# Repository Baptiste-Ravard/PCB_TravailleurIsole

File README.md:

# PCB_TravailleurIsole

# Présentation du projet :

Le projet consiste à fabriquer un badge pour les travailleurs isolés.

Celui-ci a pour but de détecter si le travailleur qui le porte fait un malaise et enverrait un signal d'alarme ainsi que la position du travailleur à l'accueil pour qu'ils puissent prévenir les secours.

Pour ce faire, on aura besoin d'un capteur d'accélération, d'un GPS et d'un LoRaWan pour envoyer les alertes.

On établit une accélération seuil selon x,y,z. Si la valeur donnée par le capteur dépasse ce seuil, on considère que le travailleur a chuté : un premier signal est envoyé à l'utilisateur. Concrètement : une LED s'allume sur le badge. L'utilisateur a alors une durée ts de quelques secondes pour appuyer sur le bouton "fausse alerte" s'il a juste trébuché ou s'il n'est pas en danger. Ce bouton va alors réinitialiser le programme et aucune alerte ne sera envoyée à l'accueil.
Si au bout de ts l'utilisateur n'a pas appuyé sur le bouton de fausse alerte, on considère que le travailleur est en danger : le badge envoie donc grâce au LoRaWan la position donnée par le GPS ainsi qu'un message d'alarme à l'accueil. Le personnel présent pourra alors prévenir les secours pour lui venir en aide.

# Lien des différentes parties du projet :
Lien ressources LoRaWan :https://github.com/OliverBELLIARD/LoRaWAN.

Lien ressources batterie :https://github.com/inassra/batterie.

Lien ressources accéléromètre et GPS :https://github.com/ValerianPRIOU/Badge-pour-travailleur-isole

# Elements à ajouter au projet :

Ajouter un buzzer qui fait du bruit quand la première alerte est envoyée pour que le travailleur s'en rende compte et puisse appuyer sur le bouton si c'est une fausse alerte.

Ajouter un deuxième bouton afin que le travailleur puisse prévenir lui même s'il ne se sent pas bien.

Valeur seuil de l'accélération complètement à revoir, notre projet était surtout basé sur la conception du PCB et faire le code pour le LoRaWan, l'accéléromètre et le GPS donc on a mit une valeur en ordre de grandeur sans trop s'y attarder. Peut être que modifier le code pour prendre la vitesse (en dérivant) au lieu de l'accélération serait une bonne piste à explorer. Prendre en compte la position selon l'axe z et étudier des différences de potentiels est aussi une idée que l'on souhaitait développer. En effet lors d'un malaise la variation de vitesse n'est pas si grande (la chute ne dure qu'1m pour le capteur) et l'accélération seuil peut se confondre avec l'accélération d'un travailleur qui passe d'une vitesse nulle à une vitesse de marche(~7km/h) ou à une vitesse de course (~12 km/h)

Notre accélération finale est la norme des accélérations selon les axes x, y et z. Ne considérer que l'accélération selon z peut aussi être envisagé.

Pour le schéma et le board du PCB, ne pas oublier de rajouter un via permettant de relier les plans de masse du dessus et du dessous du PCB. Si ce n'est pas fait les régulateurs vont sauter à cause du microprocesseur qui ne recevra pas la bonne tension.

# Ce que nous a apporté le projet :

Pendant ce projet, nous avons appris à souder, déssouder (lors des erreurs), créer un PCB complexes et les erreurs pouvants etre faites.
Nous avons aussi appris à travailler avec des personnes qu'on ne connassait pas. En tant qu'intégrateur, nous devions donner des deadlines, prendre connaissance des avancements dans chacune des équipes, mettre en connexion ces équipes et les aider si necessaire.

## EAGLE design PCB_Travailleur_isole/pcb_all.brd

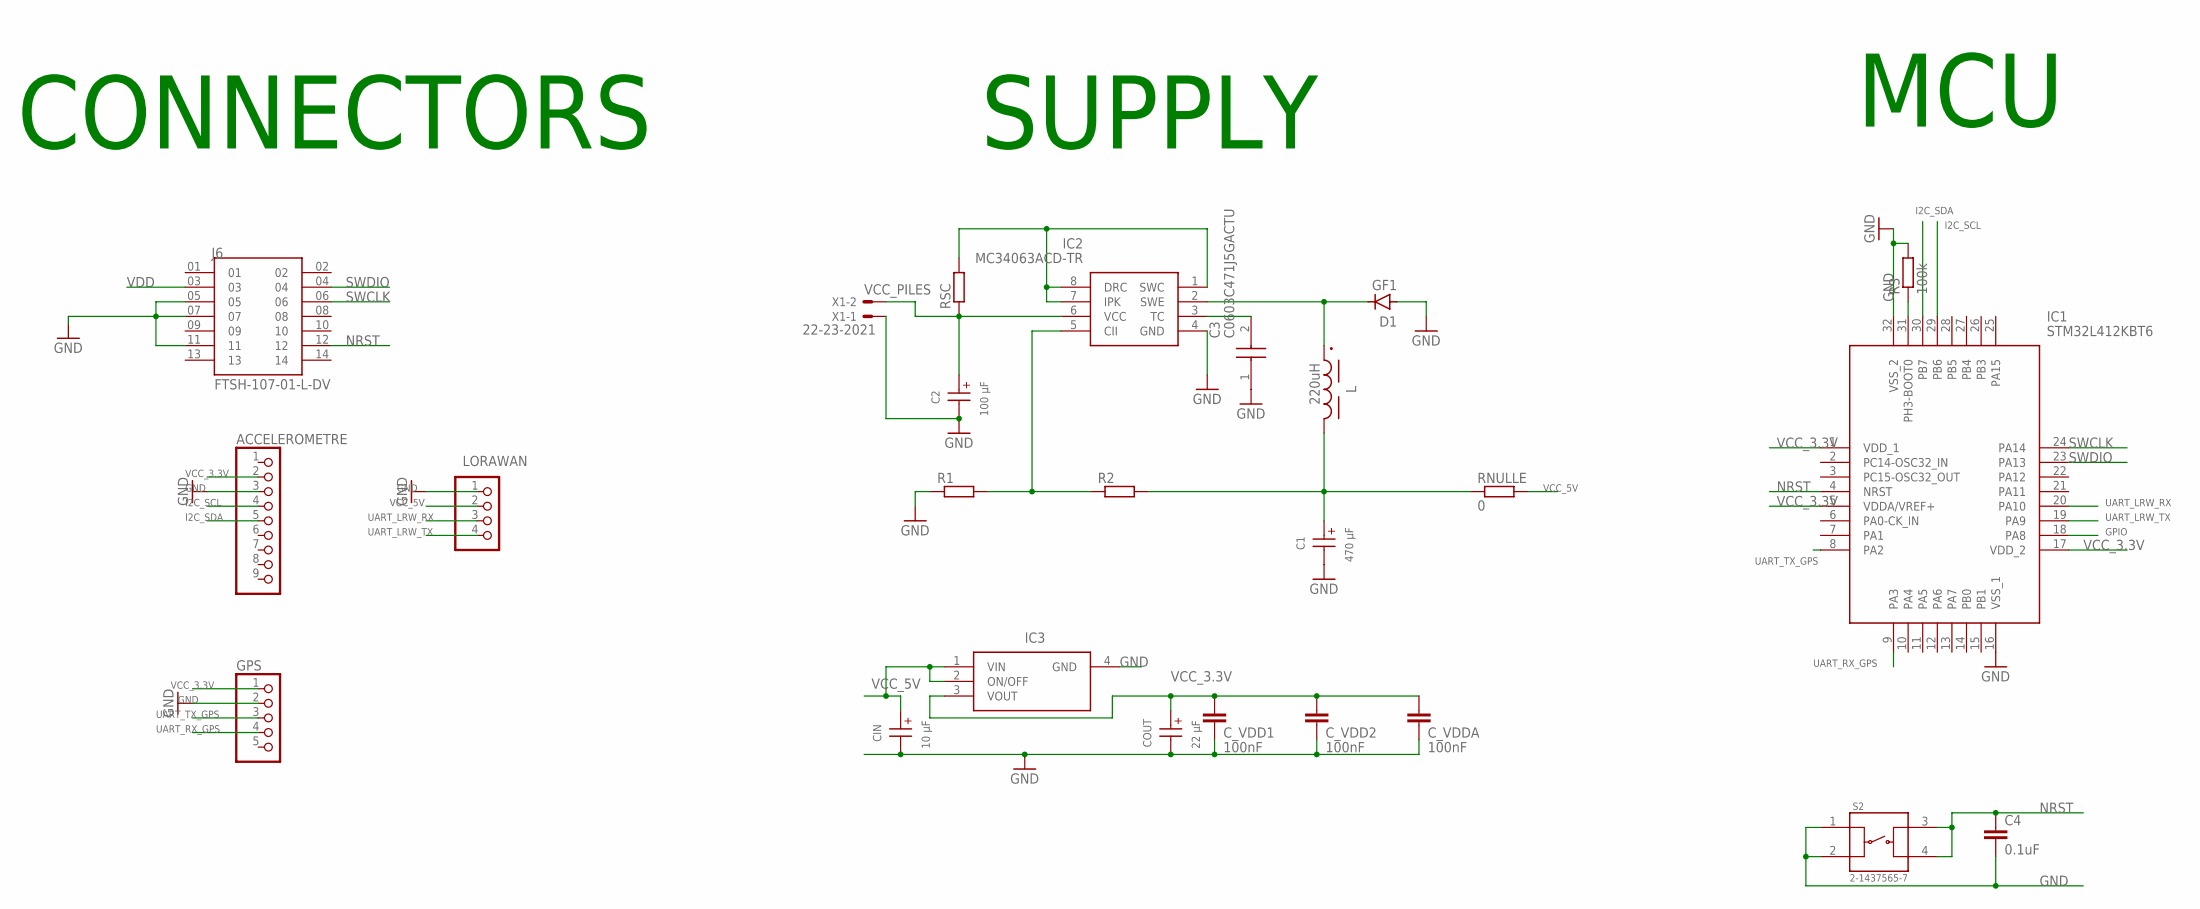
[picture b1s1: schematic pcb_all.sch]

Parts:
ACCELEROMETRE: PINHD-1X9; 1X09
C1: 470 µF; WCAP-ASLL_8X10.5(DXL)
C2: 100 µF; WCAP-ASLL_6.3X7.7(DXL)
C3: C0603C471J5GACTU; C0603
C4: 0.1uF; C0603
CIN: 10 µF; WCAP-ASLL_4X5.5(DXL)
COUT: 22 µF; WCAP-ASLL_5X5.5(DXL)
C_VDD1, C_VDD2: 100nF; C0603
C_VDDA: 100nF; C0603
D1: GF1; SMA-DO214AC
GPS: PINHD-1X5; 1X05
IC1: STM32L412KBT6; QFP80P900X900X160-32N
IC2: MC34063ACD-TR; SOIC127P600X175-8N
IC3: NCV33375ST3.3T3G; SOT230P700X175-4N
J6: FTSH-107-01-L-DV; SAMTEC_FTSH-107-01-L-DV
L: 220uH; WE-PDA_1260
LORAWAN: PINHD-1X4; 1X04
R1, R2: R-EU_R0603; R0603
R3: 100k; R0603
RNULLE: 0; R0603
RSC: R-EU_R1206W; R1206W
S2: 2-1437565-7; SW_2-1437565-7
X1: 22-23-2021

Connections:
GND: ACCELEROMETRE.3, C1.2 (-), C2.2 (-), C3.1, C4.2, CIN.2 (-), COUT.2 (-), C_VDD1.2, C_VDD2.2, C_VDDA.2, D1.A, GPS.2, IC1.16 (VSS_1), IC1.32 (VSS_2), IC2.4 (GND), IC3.4 (GND), J6.05, J6.07, J6.11, LORAWAN.1, R1.1, R3.2, S2.1, S2.2, X1.1
GPIO: IC1.18 (PA8)
I2C_SCL: ACCELEROMETRE.4, IC1.29 (PB6)
I2C_SDA: ACCELEROMETRE.5, IC1.30 (PB7)
unnamed: C1.1 (+), L.2, R2.2, RNULLE.1
unnamed: IC2.1 (SWC), IC2.7 (IPK), IC2.8 (DRC), RSC.2
unnamed: IC2.5 (CII), R1.2, R2.1
unnamed: IC1.31 (PH3-BOOT0), R3.1
unnamed: D1.K (C), IC2.2 (SWE), L.1
unnamed: C3.2, IC2.3 (TC)
NRST: C4.1, IC1.4 (NRST), J6.12, S2.3, S2.4
SWCLK: IC1.24 (PA14), J6.06
SWDIO: IC1.23 (PA13), J6.04
UART_LRW_RX: IC1.20 (PA10), LORAWAN.3
UART_LRW_TX: IC1.19 (PA9), LORAWAN.4
UART_RX_GPS: GPS.4, IC1.9 (PA3)
UART_TX_GPS: GPS.3, IC1.8 (PA2)
VCC_3.3V: ACCELEROMETRE.2, COUT.1 (+), C_VDD1.1, C_VDD2.1, C_VDDA.1, GPS.1, IC1.1 (VDD_1), IC1.5 (VDDA/VREF+), IC1.17 (VDD_2), IC3.3 (VOUT)
VCC_5V: CIN.1 (+), IC3.1 (VIN), IC3.2 (ON/OFF), LORAWAN.2, RNULLE.2
VCC_PILES: C2.1 (+), IC2.6 (VCC), RSC.1, X1.2
VDD: J6.03

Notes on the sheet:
CONNECTORS
SUPPLY
MCU

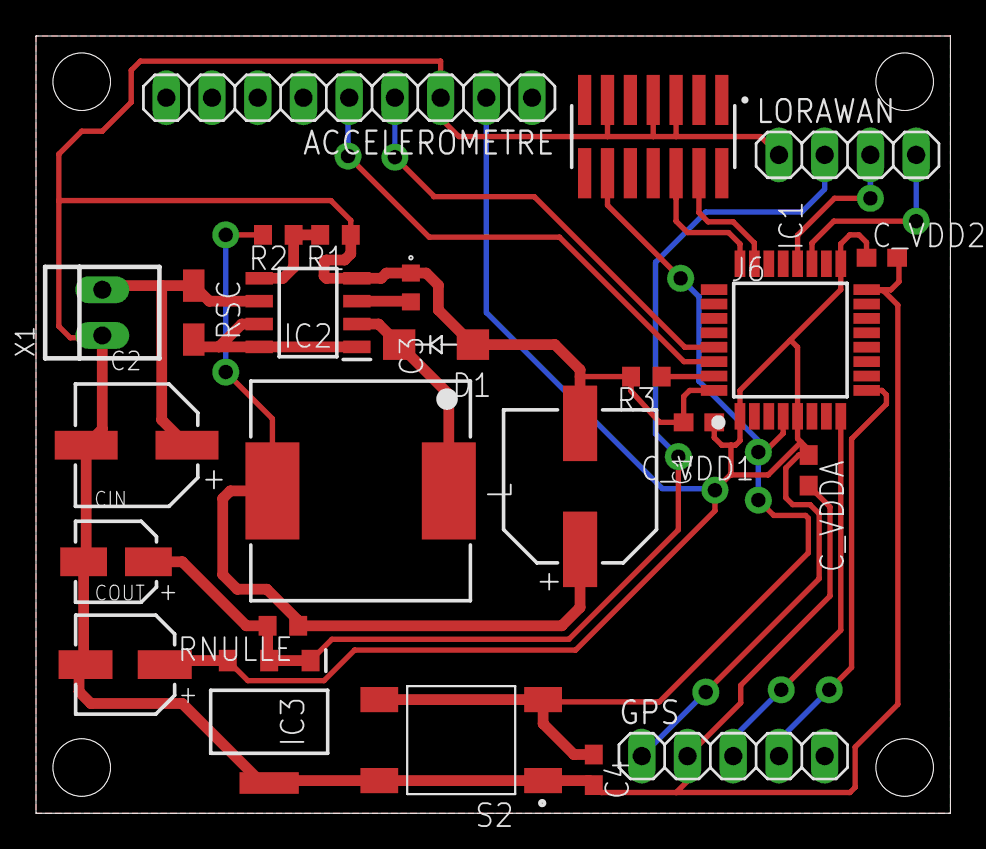
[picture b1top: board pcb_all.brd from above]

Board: 2 copper layers, 50.8 x 43.2 mm, 25 parts (0 on the bottom side), 19 nets.

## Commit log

2022-06-01 Rename A_lire.md to README.md

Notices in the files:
parts and their libraries:
C1: Copyright: Würth Elektronik
